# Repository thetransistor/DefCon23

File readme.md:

# DC801 2015 Defcon VIP Party Badge
[DC801](https://dc801.org/) and [theTransistor](http://thetransistor.com/) bring you yet another fun party badge.

##Features
- [Parallax Propeller mCU](https://www.parallax.com/product/p8x32a-d40)
- Atmega328P mCU (For analog and additional IO)
- ESP8266 (ESP-12E) WiFi Module
- Socket for XBee Serial Radio
- FTDI with Selectable Output via Bus Switch
- 3.6" LCD
  - 400x240 Resolution
  - 18-bit Color
  - ~~ILI9327~~ R61509V Chipset
- 2000 mAh LiPo Battery and Charging Circuit
- Awesome HDPE / Acrylic Case
- 2x Analog Joysticks
- Rotary Encoder
- 2x Pushbuttons
- 10x WS2812B RGB LED Pixels
- Charge / Voltage Readout Capabilities
- microSD Card

##Credits:

**Electronics Engineering**
- Compukidmike

**Original Design**
- D3c4f

**Case Manufacturing**
- [Isaac @ Rusted Friend](http://rustedfriend.com/)

**QA, Assembly, Software, Loading, Misc**
- @d3c4f
- @compukidmike
- @animcogn
- @aarobc (l3mur)
- @doktorunicorn
- @programm3rq
- @mindjuju
- @devil_bunny (yukaia)
- @nemus801
- SausageAssassn 

**Special Thanks**
- All you amazing hackers that help fund this project every year! <3
- DC801 and theTransistor Crews
- Utah Open Source

##Questions and Comments
Questions and comments can be directed towards the following forms of communication:
- #thetransistor on freenode
- d3c4f [at] thetransistor [dot] com

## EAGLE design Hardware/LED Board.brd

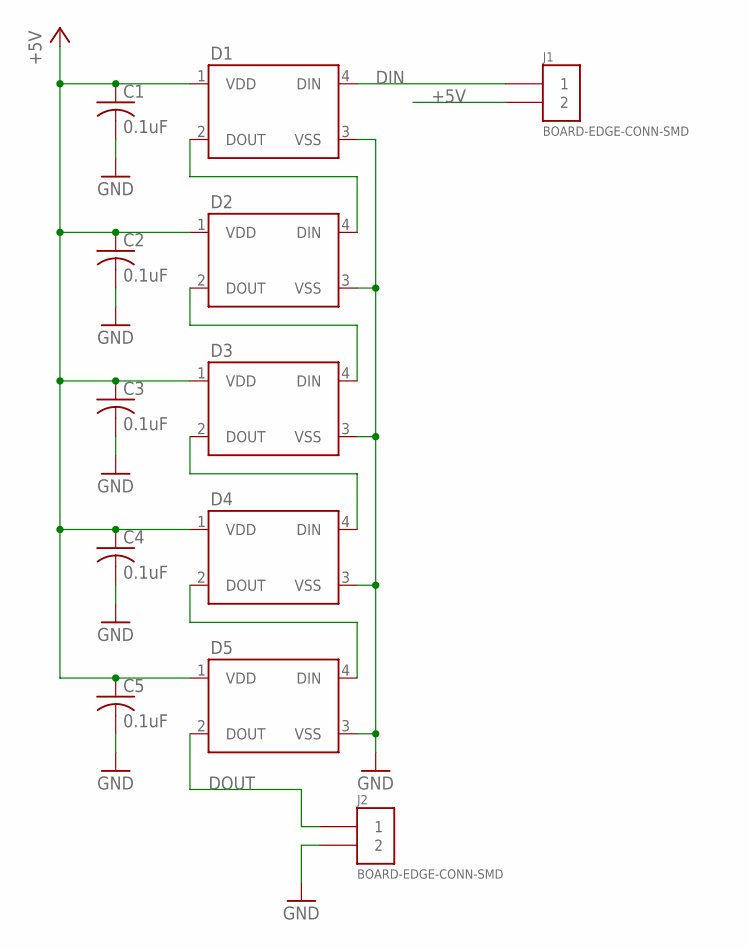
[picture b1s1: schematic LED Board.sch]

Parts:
C1, C2, C3, C4, C5: 0.1uF; C0603
D1, D2, D3, D4, D5: WS2812B
J1, J2: BOARD-EDGE-CONN-SMD; SMD-2

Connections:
+5V: C1.1, C2.1, C3.1, C4.1, C5.1, D1.1 (VDD), D2.1 (VDD), D3.1 (VDD), D4.1 (VDD), D5.1 (VDD), J1.P$2 (2)
DIN: D1.4 (DIN), J1.P$1 (1)
DOUT: D5.2 (DOUT), J2.P$1 (1)
GND: C1.2, C2.2, C3.2, C4.2, C5.2, D1.3 (VSS), D2.3 (VSS), D3.3 (VSS), D4.3 (VSS), D5.3 (VSS), J2.P$2 (2)
unnamed: D1.2 (DOUT), D2.4 (DIN)
unnamed: D2.2 (DOUT), D3.4 (DIN)
unnamed: D3.2 (DOUT), D4.4 (DIN)
unnamed: D4.2 (DOUT), D5.4 (DIN)

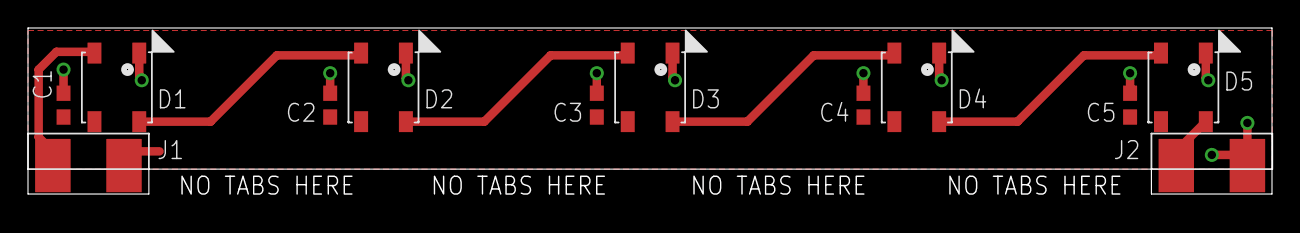
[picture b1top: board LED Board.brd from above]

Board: 2 copper layers, 88.9 x 12.6 mm, 12 parts (0 on the bottom side), 8 nets.

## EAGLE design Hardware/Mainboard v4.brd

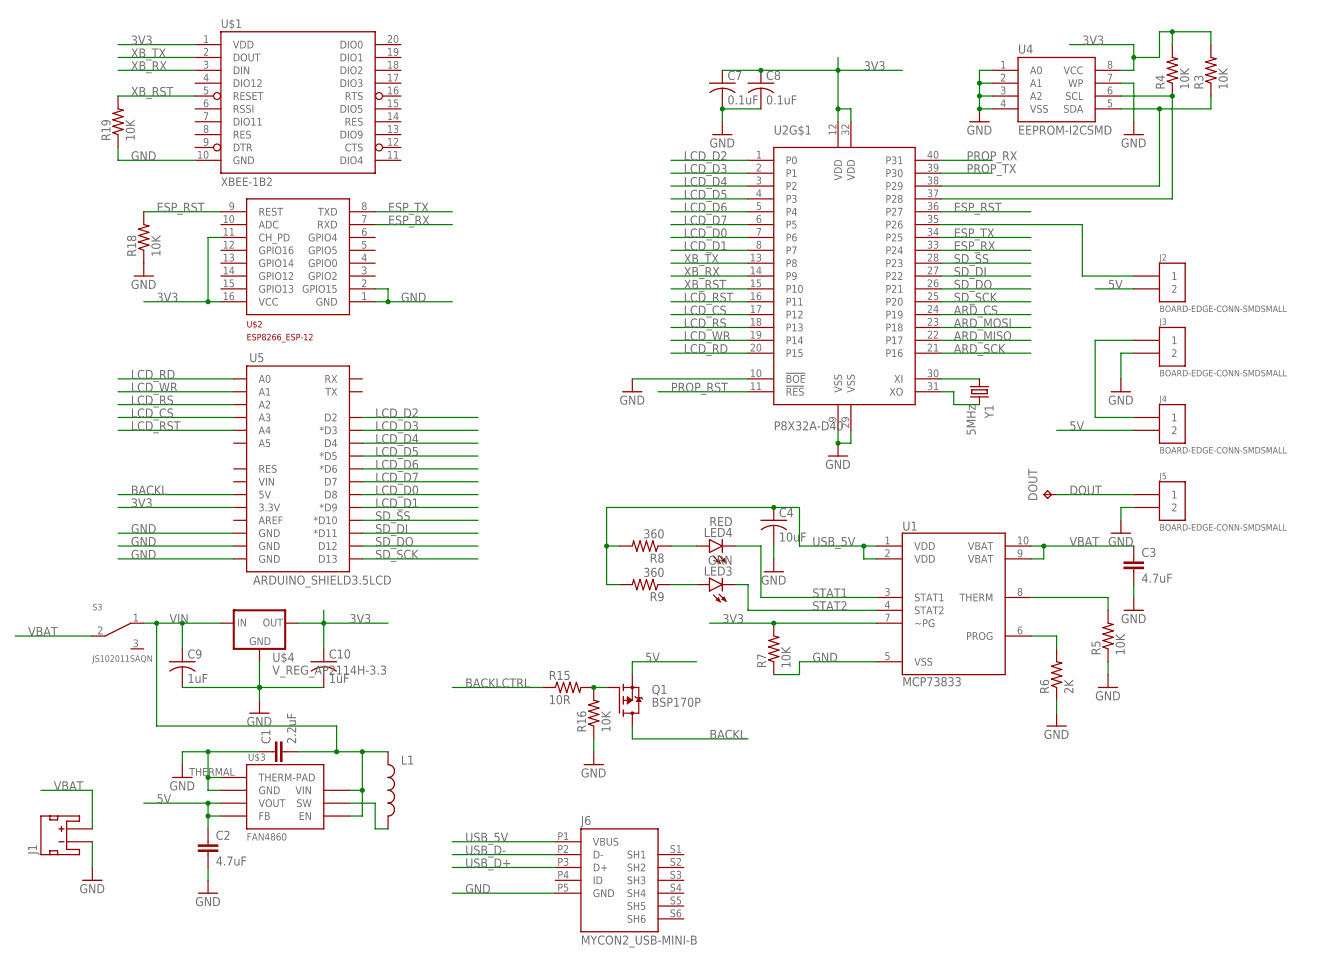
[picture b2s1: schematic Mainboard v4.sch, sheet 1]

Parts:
C1: 2.2uF; 0402-CAP
C2, C3: 4.7uF; 0603-CAP
C4: 10uF; C1206K
C7, C8: 0.1uF; C0805
C9, C10: 1uF; C1206K
DOUT: TPPAD1-13; P1-13
J1: JST_2MM_MALE; JST-2-SMD
J2, J3, J4, J5: BOARD-EDGE-CONN-SMDSMALL; SMD-2-SMALL
J6: MYCON2_USB-MINI-B; CON2_USB_MICRO_B_AT
L1: INDUCTOR0805; 0805
LED3: GRN; LED-0603
LED4: RED; LED-0603
Q1: BSP170P; SOT223
R3, R4, R5, R7, R16, R18, R19: 10K; R0603
R6: 2K; R0603
R8, R9: 360; R0603
R15: 10R; R0603
S3: JS102011SAQN; SAQN
U1: MCP73833; MSOP-10
U2: P8X32A-D40; DIP-40
U4: EEPROM-I2CSMD; SO08
U5: ARDUINO_SHIELD3.5LCD; 3.6TFT-LCD-SHIELD
U$1: XBEE-1B2; XBEE-SILK
U$2: ESP8266_ESP-12; ESP8266-ESP12E
U$3: FAN4860; 6-UMLP
U$4: V_REG_AP2114H-3.3; SOT223
Y1: 5MHz; CRYSTAL-SMD

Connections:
3V3: C7.1, C8.1, C10.1, R3.2, R4.2, R7.2, U1.7 (~PG), U2.12 (VDD), U2.32 (VDD), U4.8 (VCC), U5.3.3V, U$1.1 (VDD), U$2.11 (CH_PD), U$2.16 (VCC), U$4.2 (OUT); also elsewhere on the board
5V: C2.1, J2.P$2 (2), J4.P$2 (2), Q1.3 (S), U$3.P$2 (VOUT), U$3.P$3 (FB)
ARD_CS: U2.24 (P19); also elsewhere on the board
ARD_MISO: U2.22 (P17); also elsewhere on the board
ARD_MOSI: U2.23 (P18); also elsewhere on the board
ARD_SCK: U2.21 (P16); also elsewhere on the board
BACKL: Q1.2 (D), Q1.4 (D), U5.5V
BACKLCTRL: R15.1; also elsewhere on the board
DOUT: DOUT.TP, J5.P$1 (1)
ESP_RST: R18.2, U2.36 (P27), U$2.9 (REST)
ESP_RX: U2.33 (P24), U$2.7 (RXD)
ESP_TX: U2.34 (P25), U$2.8 (TXD)
GND: C1.1, C2.2, C3.2, C4.2, C7.2, C8.2, C9.2, C10.2, J1.1 (-), J3.P$2 (2), J5.P$2 (2), J6.P5 (GND), R5.1, R6.1, R7.1, R16.1, R18.1, R19.1, U1.5 (VSS), U2.9 (VSS), U2.10 (!BOE), U2.29 (VSS), U4.1 (A0), U4.2 (A1), U4.3 (A2), U4.4 (VSS), U4.7 (WP), U5.GND@0 (GND), U5.GND@1 (GND), U5.GND@2 (GND), U$1.10 (GND), U$2.1 (GND), U$2.2 (GPIO15), U$3.P$1 (GND), U$3.THERMAL (THERM-PAD), U$4.1 (GND); also elsewhere on the board
LCD_CS: U2.17 (P12), U5.A3
LCD_D0: U2.7 (P6), U5.D8
LCD_D1: U2.8 (P7), U5.D9 (*D9)
LCD_D2: U2.1 (P0), U5.D2
LCD_D3: U2.2 (P1), U5.D3 (*D3)
LCD_D4: U2.3 (P2), U5.D4
LCD_D5: U2.4 (P3), U5.D5 (*D5)
LCD_D6: U2.5 (P4), U5.D6 (*D6)
LCD_D7: U2.6 (P5), U5.D7
LCD_RD: U2.20 (P15), U5.A0
LCD_RS: U2.18 (P13), U5.A2
LCD_RST: U2.16 (P11), U5.A4
LCD_WR: U2.19 (P14), U5.A1
unnamed: J3.P$1 (1), J4.P$1 (1)
unnamed: J2.P$1 (1), U2.35 (P26)
unnamed: R4.1, U2.37 (P28), U4.6 (SCL)
unnamed: R3.1, U2.38 (P29), U4.5 (SDA)
unnamed: U2.30 (XI), Y1.P$1 (1)
unnamed: U2.31 (XO), Y1.P$2 (2)
unnamed: LED4.A, R8.1
unnamed: LED3.A, R9.1
unnamed: R5.2, U1.8 (THERM)
unnamed: Q1.1 (G), R15.2, R16.2
unnamed: R6.2, U1.6 (PROG)
unnamed: L1.2, U$3.P$5 (SW)
PROP_RST: U2.11 (!RES)
PROP_RX: U2.40 (P31); also elsewhere on the board
PROP_TX: U2.39 (P30); also elsewhere on the board
SD_DI: U2.27 (P22), U5.D11 (*D11)
SD_DO: U2.26 (P21), U5.D12
SD_SCK: U2.25 (P20), U5.D13
SD_SS: U2.28 (P23), U5.D10 (*D10)
STAT1: LED4.C, U1.3 (STAT1); also elsewhere on the board
STAT2: LED3.C, U1.4 (STAT2); also elsewhere on the board
USB_5V: C4.1, J6.P1 (VBUS), R8.2, R9.2, U1.1 (VDD), U1.2 (VDD); also elsewhere on the board
USB_D+: J6.P3 (D+); also elsewhere on the board
USB_D-: J6.P2 (D-); also elsewhere on the board
VBAT: C3.1, J1.2 (+), S3.2, U1.9 (VBAT), U1.10 (VBAT); also elsewhere on the board
VIN: C1.2, C9.1, L1.1, S3.1, U$3.P$4 (EN), U$3.P$6 (VIN), U$4.3 (IN)
XB_RST: R19.2, U2.15 (P10), U$1.5 (RESET)
XB_RX: U2.14 (P9), U$1.3 (DIN)
XB_TX: U2.13 (P8), U$1.2 (DOUT)

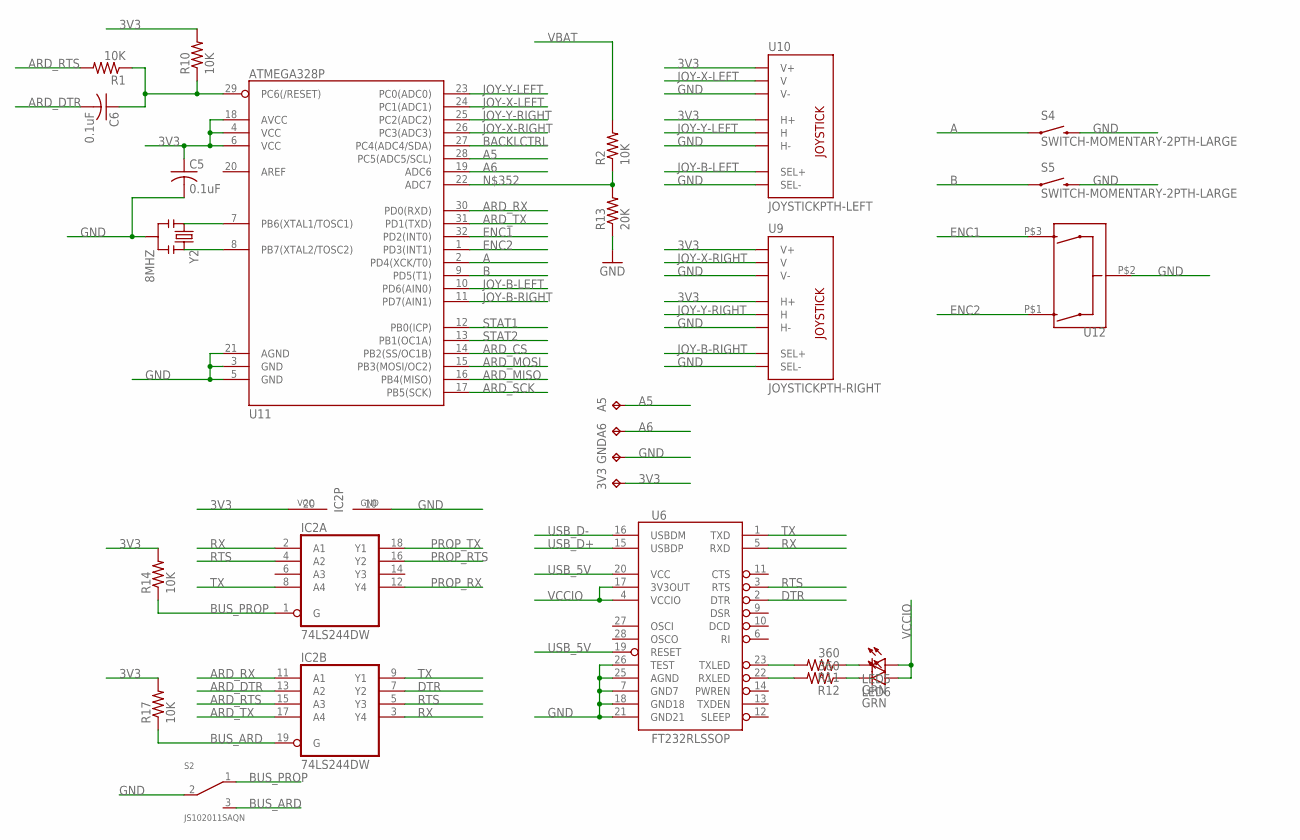
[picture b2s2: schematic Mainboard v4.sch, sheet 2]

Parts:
3V3: TPPAD1-13; P1-13
A5, A6: TPPAD1-13; P1-13
C5, C6: 0.1uF; C0805
GND: TPPAD1-13; P1-13
IC2: 74LS244DW; SO20W
LED5, LED6: GRN; LED-0603
R1, R2, R10, R14, R17: 10K; R0603
R11, R12: 360; R0603
R13: 20K; R0603
S2: JS102011SAQN; SAQN
S4, S5: SWITCH-MOMENTARY-2PTH-LARGE; TACTILE-PTH-LARGE
U6: FT232RLSSOP; SSOP28DB
U9: JOYSTICKPTH-RIGHT; JOYSTICK
U10: JOYSTICKPTH-LEFT; JOYSTICK
U11: ATMEGA328P; TQFP32-08
U12: ENCODER-QUADRATURE; ENCODER-12MM-VERT-SQ
Y2: 8MHZ; RESONATOR-AWSCR-CV

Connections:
3V3: 3V3.TP, C5.1, IC2.20 (VCC), R10.2, R14.2, R17.2, U9.H1 (H+), U9.V1 (V+), U10.H1 (H+), U10.V1 (V+), U11.4 (VCC), U11.6 (VCC), U11.18 (AVCC); also elsewhere on the board
A: S4.P$1 (1), U11.2 (PD4(XCK/T0))
A5: A5.TP, U11.28 (PC5(ADC5/SCL))
A6: A6.TP, U11.19 (ADC6)
ARD_CS: U11.14 (PB2(SS/OC1B)); also elsewhere on the board
ARD_DTR: C6.2, IC2.13 (A2)
ARD_MISO: U11.16 (PB4(MISO)); also elsewhere on the board
ARD_MOSI: U11.15 (PB3(MOSI/OC2)); also elsewhere on the board
ARD_RTS: IC2.15 (A3), R1.2
ARD_RX: IC2.11 (A1), U11.30 (PD0(RXD))
ARD_SCK: U11.17 (PB5(SCK)); also elsewhere on the board
ARD_TX: IC2.17 (A4), U11.31 (PD1(TXD))
B: S5.P$1 (1), U11.9 (PD5(T1))
BACKLCTRL: U11.27 (PC4(ADC4/SDA)); also elsewhere on the board
BUS_ARD: IC2.19 (G), R17.1, S2.3
BUS_PROP: IC2.1 (G), R14.1, S2.1
DTR: IC2.7 (Y2), U6.2 (DTR)
ENC1: U11.32 (PD2(INT0)), U12.P$3 (B)
ENC2: U11.1 (PD3(INT1)), U12.P$1 (A)
GND: C5.2, GND.TP, IC2.10 (GND), R13.1, S2.2, S4.P$2 (2), S5.P$2 (2), U6.7 (GND7), U6.18 (GND18), U6.21 (GND21), U6.25 (AGND), U6.26 (TEST), U9.B2A (SEL-), U9.H3 (H-), U9.V3 (V-), U10.B2A (SEL-), U10.H3 (H-), U10.V3 (V-), U11.3 (GND), U11.5 (GND), U11.21 (AGND), U12.P$2 (C), Y2.P$2 (2); also elsewhere on the board
JOY-B-LEFT: U10.B1A (SEL+), U11.10 (PD6(AIN0))
JOY-B-RIGHT: U9.B1A (SEL+), U11.11 (PD7(AIN1))
JOY-X-LEFT: U10.V2 (V), U11.24 (PC1(ADC1))
JOY-X-RIGHT: U9.V2 (V), U11.26 (PC3(ADC3))
JOY-Y-LEFT: U10.H2 (H), U11.23 (PC0(ADC0))
JOY-Y-RIGHT: U9.H2 (H), U11.25 (PC2(ADC2))
unnamed: R11.2, U6.23 (TXLED)
unnamed: R12.2, U6.22 (RXLED)
unnamed: LED5.C, R11.1
unnamed: LED6.C, R12.1
unnamed: U11.7 (PB6(XTAL1/TOSC1)), Y2.P$1 (1)
unnamed: U11.8 (PB7(XTAL2/TOSC2)), Y2.P$3 (3)
unnamed: C6.1, R1.1, R10.1, U11.29 (PC6(/RESET))
unnamed: R2.1, R13.2, U11.22 (ADC7)
PROP_RTS: IC2.16 (Y2)
PROP_RX: IC2.12 (Y4); also elsewhere on the board
PROP_TX: IC2.18 (Y1); also elsewhere on the board
RTS: IC2.4 (A2), IC2.5 (Y3), U6.3 (RTS)
RX: IC2.2 (A1), IC2.3 (Y4), U6.5 (RXD)
STAT1: U11.12 (PB0(ICP)); also elsewhere on the board
STAT2: U11.13 (PB1(OC1A)); also elsewhere on the board
TX: IC2.8 (A4), IC2.9 (Y1), U6.1 (TXD)
USB_5V: U6.19 (RESET), U6.20 (VCC); also elsewhere on the board
USB_D+: U6.15 (USBDP); also elsewhere on the board
USB_D-: U6.16 (USBDM); also elsewhere on the board
VBAT: R2.2; also elsewhere on the board
VCCIO: LED5.A, LED6.A, U6.4 (VCCIO), U6.17 (3V3OUT)

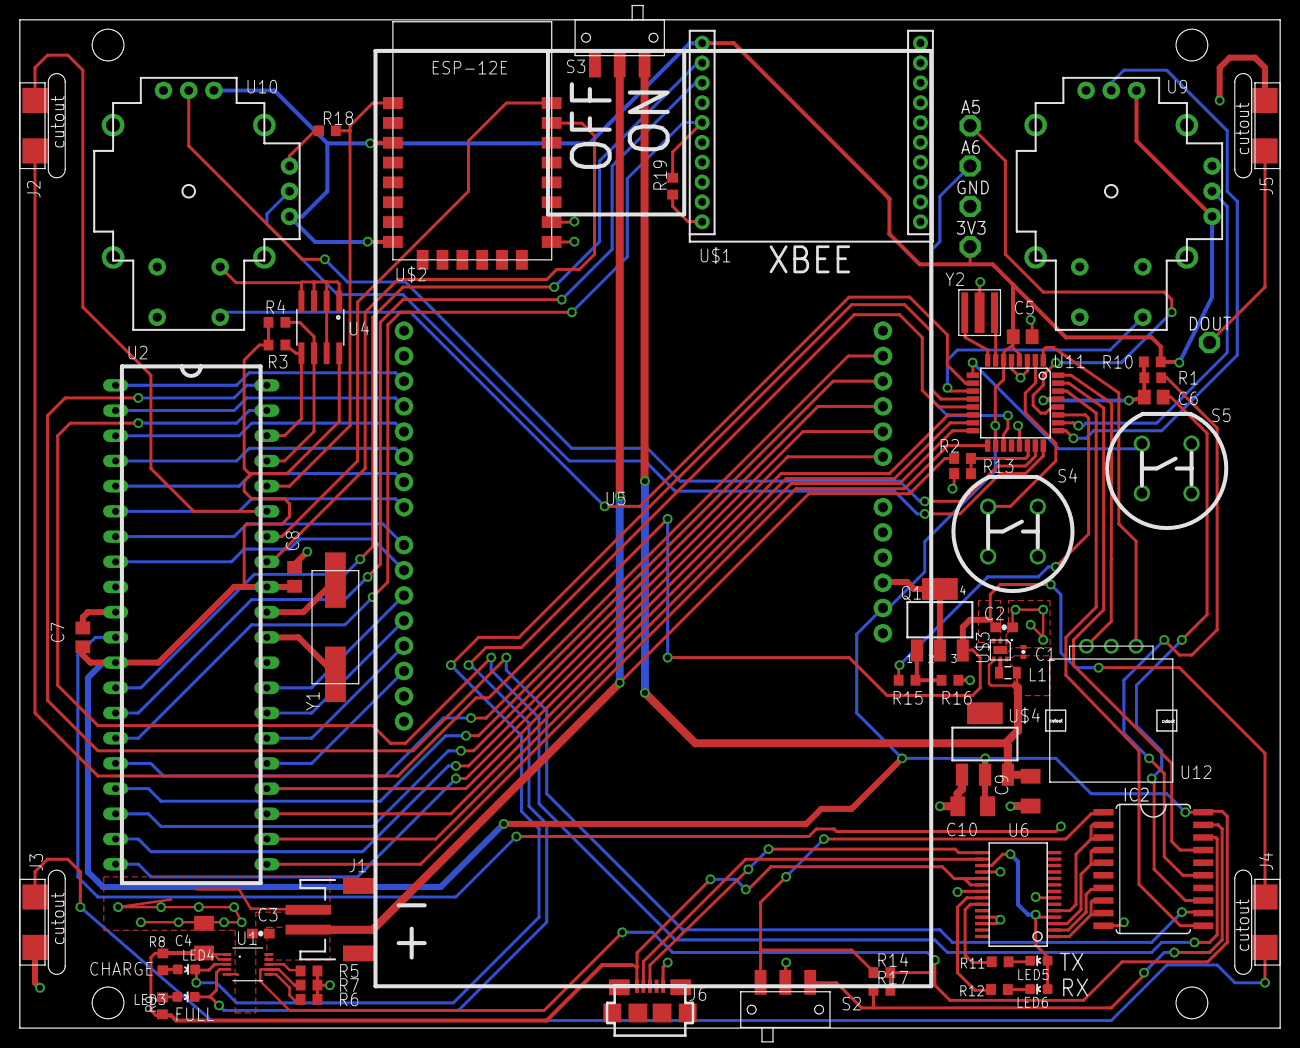
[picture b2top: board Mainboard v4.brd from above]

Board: 5 copper layers, 126.9 x 101.5 mm, 66 parts (0 on the bottom side), 85 nets.

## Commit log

2015-08-10 Initial Commit. More soon

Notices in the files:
parts and their libraries:
SparkFun-LED: Licensing: Creative Commons ShareAlike 4.0 International - https://creativecommons.org/licenses/by-sa/4.0
